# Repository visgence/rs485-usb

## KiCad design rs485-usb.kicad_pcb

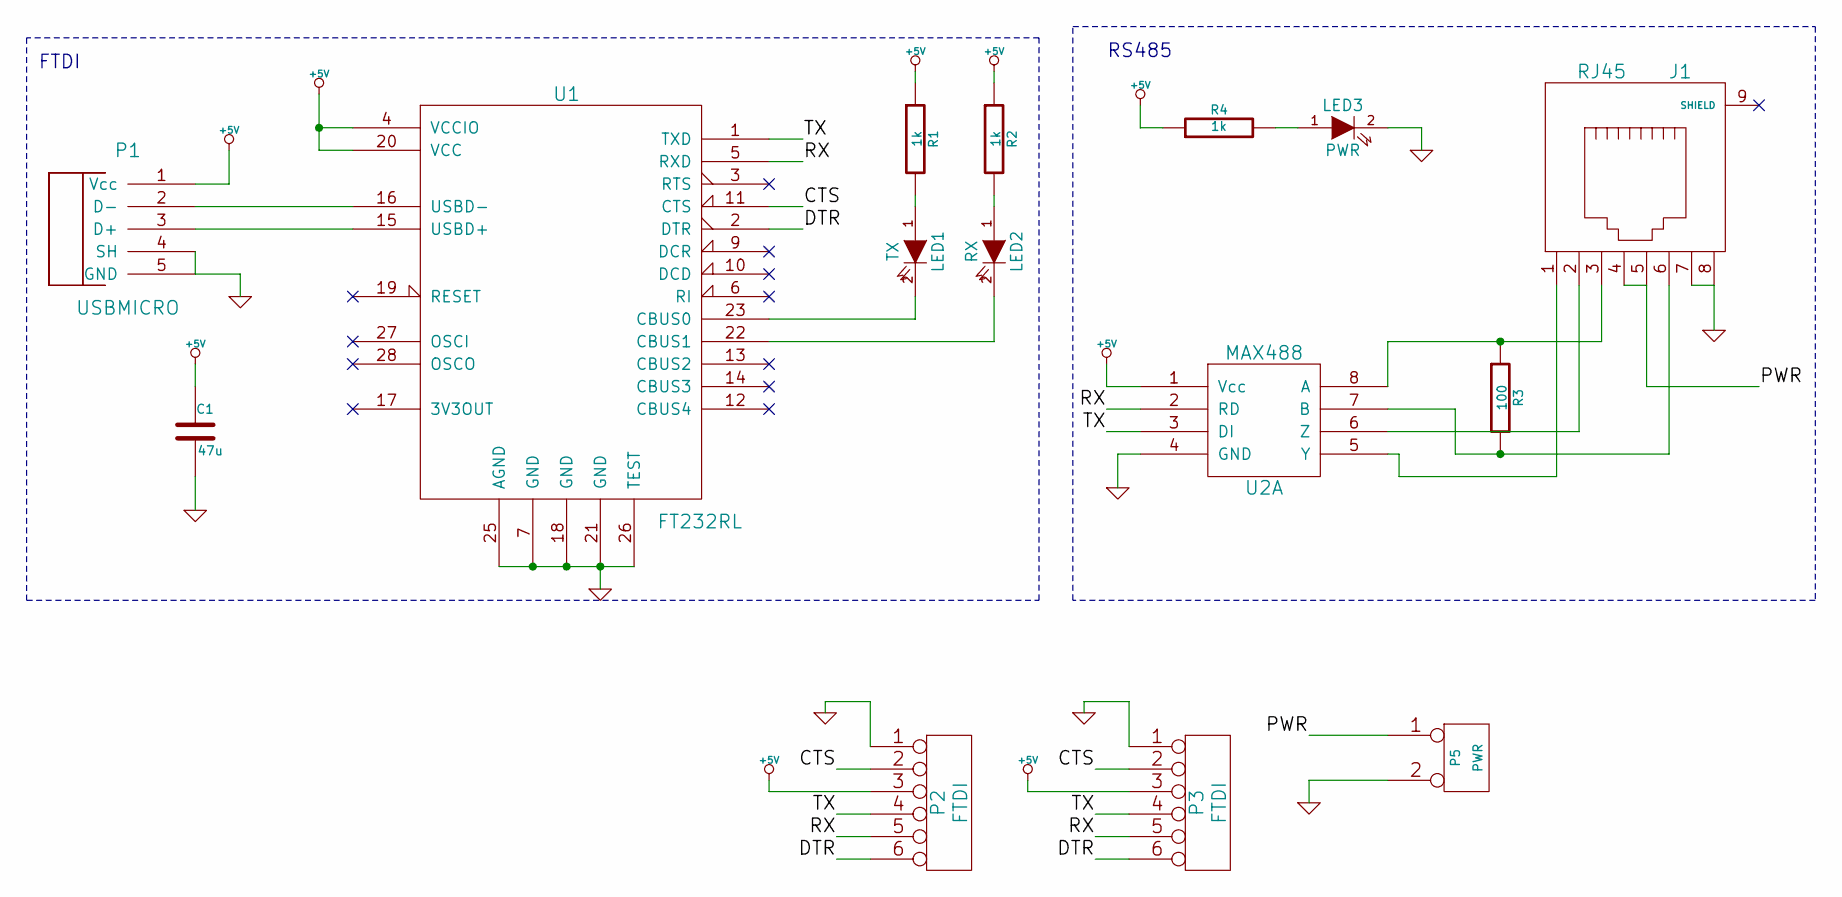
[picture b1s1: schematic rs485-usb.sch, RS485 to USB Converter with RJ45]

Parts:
C1: 47u
J1: RJ45
LED1: TX
LED2: RX
LED3: PWR
P1: USBMICRO
P2, P3: FTDI
P5: PWR
R1, R2, R4: 1k
R3: 100
U1: FT232RL
U2: MAX488

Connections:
+5V: C1.1, P1.1 (Vcc), P2.3, P3.3, R1.1, R2.1, R4.1, U1.4 (VCCIO), U1.20 (VCC), U2.1 (Vcc)
/CTS: P2.2, P3.2, U1.11 (CTS)
/DTR: P2.6, P3.6, U1.2 (DTR)
/PWR: J1.4, J1.5, P5.1
/RX: P2.5, P3.5, U1.5 (RXD), U2.2 (RD)
/TX: P2.4, P3.4, U1.1 (TXD), U2.3 (DI)
GND: C1.2, J1.7, J1.8, LED3.2 (K), P1.4 (SH), P1.5 (GND), P2.1, P3.1, P5.2 (PM), U1.7 (GND), U1.18 (GND), U1.21 (GND), U1.25 (AGND), U1.26 (TEST), U2.4 (GND)
unnamed: LED2.2 (K), U1.22 (CBUS1)
unnamed: LED1.2 (K), U1.23 (CBUS0)
unnamed: LED1.1 (A), R1.2
unnamed: LED2.1 (A), R2.2
unnamed: P1.2 (D-), U1.16 (USBD-)
unnamed: P1.3 (D+), U1.15 (USBD+)
unnamed: LED3.1 (A), R4.2
unnamed: J1.2, U2.6 (Z)
unnamed: J1.1, U2.5 (Y)
unnamed: J1.3, R3.1, U2.8 (A)
unnamed: J1.6, R3.2, U2.7 (B)

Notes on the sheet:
RS485
FTDI

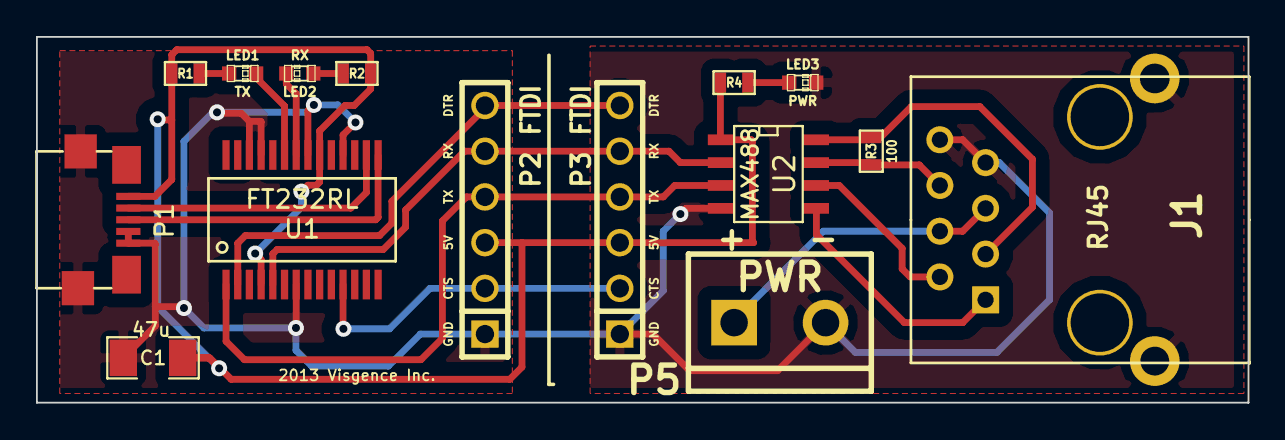
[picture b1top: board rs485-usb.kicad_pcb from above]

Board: 2 copper layers, 67.3 x 20.3 mm, 16 parts (1 on the bottom side), 18 nets.

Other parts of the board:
G2: LOGO; OSHW_LOGO

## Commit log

2013-11-19 First commit of schematic
2013-11-19 Created first pass at board
2013-11-20 Filled board, added logos text
2013-11-20 Added gerber rules
